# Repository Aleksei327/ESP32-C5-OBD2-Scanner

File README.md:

# ESP32-C5 OBD2 Scanner

[Русская версия](README.ru.md)

A DIY dual-CAN OBD2 diagnostic adapter built on the Seeed XIAO ESP32-C5, together with a read-only Android app. The first target is my own Citroën C3 II (2011, 1.4 KFT): ECU list, fault codes (read and clear), live data, freeze frames, a bus monitor and a PDF report. Other cars are added through a JSON knowledge base, without changing the firmware.

> **Status (November 2026): working, tested on the car.** Board v1 is built into its OBD2 enclosure, the firmware and app 0.1.5 are finished for the C3 II, and the whole chain has been used on the car: on 2 and 3 November full scans found 10 ECUs, fault codes were read with their texts, live data and an A/C test were recorded. Release: [v1.0](https://github.com/Aleksei327/ESP32-C5-OBD2-Scanner/releases/tag/v1.0).

## What works

- **Hardware:** single-sided 40 × 60 mm home-etched board in an OBD2 enclosure. Measured: on the car's OBD socket 13.4 V engine off and 14.4 V running; on the bench 4.95 V after the LM2596 and 4.83 V at the XIAO. The battery voltage reads within 0.05 V. Both CAN channels pass the self-test; the transmitters stay off in hardware until the firmware enables them.
- **Firmware** (ESP-IDF 6.1): Wi-Fi access point with its own password, WebSocket protocol, both CAN channels (OBD 6/14 and 3/8), ISO-TP with the PSA "response pending" handled, bus monitor, battery voltage, USB console with a self-test.
- **App 0.1.5** (Android): auto scan of every ECU in the knowledge base; ECU model recognised by part number; fault codes with texts from PSA-RE, the generic SAE list and, if built locally, the PSA code list in Russian and English; fault clearing; identification, live data, settings (read only); gauges, numbers and charts; bus monitor; PDF report. Scans are saved on the phone with a history (10 per car), a single module can be rescanned, and the garage and saved scans open without the adapter. The phone keeps its mobile internet while on the adapter's Wi-Fi.
- **Remote work:** a computer at home reaches the adapter at the car through the phone and a Cloudflare tunnel; `remote/scan.py` writes a full read-only scan to a report.
- **Simulator:** a C3 II in Python, to develop and test the app without the car.

Next: CAN-FD transceivers in board v2, and more cars through the knowledge base.

## The app

| | | |
| --- | --- | --- |
|  |  |  |
|  |  |  |

App 0.1.3 in English. For these screenshots it is connected to the adapter simulator ([`sim/`](sim/README.md)), not to the car, so the ECUs and values are simulated.

## The board

| | | |
| --- | --- | --- |
|  |  |  |

The real board from the copper side (two SN65HVD230, the LM2596 and the SMD parts are on this side) and the KiCad 3D view of the component side. Schematic and layout: [`hardware/scaner_v1/`](hardware/scaner_v1/README.md).

## Key decisions

| What | Choice | Why |
| --- | --- | --- |
| MCU | Seeed XIAO ESP32-C5 | two CAN (TWAI) controllers, both CAN-FD capable; Wi-Fi 6 on 2.4 and 5 GHz; BLE; 8 MB PSRAM |
| CAN channel A | OBD 6/14 | legislated OBD-II (engine) |
| CAN channel B | OBD 3/8 | PSA Diag-on-CAN through the BSI, access to every ECU |
| Transceivers | 2 × SN65HVD230 (SOIC-8), desoldered from Waveshare modules | 3.3 V, enough for the C3; Rs on D9/D5 with pull-ups gives a hardware listen-only mode. CAN-FD transceivers in v2 |
| Power | OBD 16 → fuse → HS1M → IRFB4110 source follower (≤ 27 V) → LM2596S-ADJ (4.9 V) → SS34 (+ 1.5KE6.8CA TVS) → 3.3 V LDO on the XIAO | all from parts in stock; survives a 24 V jump start and surges up to 100 V |
| Hardware | own single-sided 40 × 60 mm board inside an OBD2 enclosure with a built-in connector; tracks on the bottom only, no jumpers | one dongle, no cables |
| App | Flutter for Android (Galaxy A55): read-only plus fault-code clearing; two themes; Russian and English | |
| Link | Wi-Fi, JSON over WebSocket; the adapter is a "dumb" transport, all logic lives in the app | a new car is a new JSON file |

## Repository

| Folder | Contents |
| --- | --- |
| [`hardware/scaner_v1/`](hardware/scaner_v1/README.md) | KiCad 10 project: schematic, PCB, footprints, 3D models, and the Python scripts that generate and route the board; PDF exports in `build/` |
| [`firmware/scaner_fw/`](firmware/scaner_fw/README.md) | ESP-IDF 6.1 adapter firmware: Wi-Fi access point and WebSocket server for the app, both CAN channels, battery voltage |
| [`app/`](app/README.md) | Flutter app |
| [`sim/`](sim/README.md) | Python simulator of the adapter with a C3 attached, to develop the app without hardware or a car |
| [`remote/`](remote/README.md) | remote assistant: a computer at home works with the adapter at the car through the phone and a Cloudflare tunnel |
| [`DOCS/en/`](DOCS/en/) | documentation in English ([`DOCS/`](DOCS/) — Russian originals) |

## Documentation

- [Board v1](DOCS/en/board-v1.md): block diagram, enclosure, OBD wiring, pin assignment, layout notes, first power-up
- [Input protection](DOCS/en/power-protection.md): what the car's electrical system does to pin 16 and how the board survives it
- [LM2596 DC-DC](DOCS/en/dc-dc-5v.md): parts and values
- [XIAO ESP32-C5](DOCS/en/xiao-esp32c5.md): pinout and which pins are used
- [SN65HVD230 transceiver](DOCS/en/can-sn65hvd230.md): wiring, listen-only mode, terminators
- [Adapter ↔ app protocol](DOCS/en/protocol.md)
- [Parts list](DOCS/en/parts-list.md)

PDF exports: [schematic](hardware/scaner_v1/build/scaner_v1.pdf), [placement and copper](hardware/scaner_v1/build/pcb_placement.pdf), [bottom copper 1:1 for etching](hardware/scaner_v1/build/pcb_bottom_cu.pdf).

## What is known about the C3 (PSA, AEE2004/2010 architecture)

- Full diagnostics run on pins **3/8** (Diag-on-CAN, 500 kbit/s) through the BSI. Pins **6/14** only give legislated engine OBD-II.
- Protocols: PSA-style KWP2000 (almost every ECU of the C3 II) and UDS, both over CAN (ISO-TP). The app finds out by itself which one an ECU speaks and recognises the ECU model by its part number.
- ECU addresses (request:response): BSI `752:652`, engine `6A8:688`, ABS/ESP `6AD:68D`, airbag `744:644`, instrument cluster `75F:65F`.
- On our C3 II 1.4 KFT the engine ECU is a Valeo V34 (KWP, session `81`). Answering: BSI, engine, ABS MK70, power steering, steering-column switches, instrument cluster, display, radio, airbag, seat-belt indicator and the battery sensor (the last one often answers "busy" or stays silent).
- Terminators: pins 6–14 already have both in the car (57 Ω), pins 3–8 only the BSI one (128 Ω), so the board has R8 fitted and R7 left out.

## Rules

1. The app only reads. The only write is clearing fault codes.
2. Airbag and ABS: read only. Emissions systems are not touched.
3. The adapter is not left in the car: pin 16 is powered from the battery at all times.

## Credits and third-party work

No third-party code is copied into this repository. The app's knowledge base is generated from PSA-RE data, with extra fault-code texts from ludwig-v and OBD Codes List (see below). These projects, tools and libraries were used or consulted:

- [prototux/PSA-RE](https://github.com/prototux/PSA-RE) (Apache-2.0) — PSA electronics reverse engineering: which ECUs the C3 II has, their addresses, protocols, part numbers, data records and fault-code texts. The app's knowledge base ([`app/assets/kb/`](app/assets/kb/)) is built from it by [`app/tool/build_kb.py`](app/tool/build_kb.py); its licence text ships with the data.
- [ludwig-v/arduino-psa-diag](https://github.com/ludwig-v/arduino-psa-diag) (GPL-3.0) — PSA ECU addresses ([ECU_LIST.md](https://github.com/ludwig-v/arduino-psa-diag/blob/master/ECU_LIST.md)) and KWP/UDS commands, used as a cross-check. Its fault-code lists fill the codes PSA-RE has no text for (mostly the BSI); they ship as a separate data file under GPL-3.0, [`app/assets/kb/c3_ii_dtc_gpl.json`](app/assets/kb/c3_ii_dtc_gpl.json), with the licence text next to it.
- [OBD Codes List](https://obdcodeslist.com/code-data.html) via [tekseport/obd2-codes](https://github.com/tekseport/obd2-codes) — generic SAE J2012 fault-code texts, shown when an ECU's own list has no text for a code. Code data from OBD Codes List, https://obdcodeslist.com/code-data.html
- [KiCad](https://www.kicad.org/) and its official symbol, footprint and 3D-model libraries.
- [Freerouting](https://github.com/freerouting/freerouting) — used to explore routing (`hardware/scaner_v1/tools/route.py`); the final layout is routed by hand.
- [ESP-IDF](https://github.com/espressif/esp-idf) (Espressif) — firmware framework; [Seeed Studio wiki](https://wiki.seeedstudio.com/xiao_esp32c5_getting_started/) — XIAO ESP32-C5 pinout.
- [Flutter](https://flutter.dev/) and the Dart packages listed in [`app/pubspec.yaml`](app/pubspec.yaml): web_socket_channel, flutter_svg, google_fonts, shared_preferences, intl, image_picker, path_provider, pdf, share_plus.
- Fonts [Exo 2](https://fonts.google.com/specimen/Exo+2) and [IBM Plex](https://github.com/IBM/plex), SIL Open Font License 1.1 (licence texts in `app/assets/google_fonts/`).
- [websockets](https://github.com/python-websockets/websockets) — the simulator's WebSocket server.
- Datasheets and application data: Texas Instruments (SN65HVD230, LM2596), Espressif (ESP32-C5), Waveshare (SN65HVD230 CAN Board schematic).

Each of these keeps its own licence.

## License

See [NOTICE.md](NOTICE.md) and [LICENSE](LICENSE) (CC BY-NC-ND 4.0, with permission to build one unit for yourself).

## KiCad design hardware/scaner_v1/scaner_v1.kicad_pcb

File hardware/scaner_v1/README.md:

# Board v1 — KiCad project

[Русская версия](README.ru.md)

KiCad 10 project of the adapter board: 40 × 60 mm, single-sided (all tracks on the bottom copper, no wire jumpers), designed for home etching and built into an OBD2 enclosure. Description and design notes: [DOCS/en/board-v1.md](../../DOCS/en/board-v1.md).

| Top | Bottom |
| --- | --- |
|  |  |
|  |  |

Top row: KiCad 3D. Bottom row: the board as built, in its enclosure and from the copper side.

## Files

| Path | Contents |
| --- | --- |
| `scaner_v1.kicad_sch`, `scaner_v1.kicad_pcb`, `scaner_v1.kicad_pro` | schematic, board, project (design rules: 0.8 mm tracks, 0.4 mm clearance) |
| `scaner.pretty/` | project footprints: XIAO ESP32-C5 on two 1×7 sockets, DO-35 zener at 5.08 mm pitch, OBD2 enclosure outline |
| `scaner.3dshapes/` | hand-written 3D models (VRML) for parts missing from the KiCad library |
| `build/*.pdf` | schematic, placement with copper, bottom copper 1:1 for etching |
| `tools/` | Python scripts that generate everything (see below) |

## The board is generated, not drawn by hand

The schematic, placement and routing are produced by scripts, so a change is made in the script and everything is regenerated:

```sh
python tools/gen_schematic.py        # parts, nets, project footprints -> scaner_v1.kicad_sch
python tools/check_netlist.py        # ERC and netlist check against tools/expected_nets.json
"C:\Program Files\KiCad\10.0\bin\python.exe" tools/gen_pcb.py       # placement (PLACE table), pad rules, keep-outs
"C:\Program Files\KiCad\10.0\bin\python.exe" tools/hand_route.py    # tracks from tools/routes.py, ground pour, DRC
python tools/gen_3d.py               # 3D models into scaner.3dshapes/
```

- `routes.py` — every track as a list of points (or `REF.pad` references) with its width.
- `view_board.py` — an SVG view of the board with net names on the pads, ratsnest and DRC markers; handy while routing.
- `route.py` — Freerouting experiment kept for reference; it overwrites the hand routing.

Manual edits made in KiCad are overwritten by the next `gen_pcb.py` / `hand_route.py` run — carry them over into `routes.py` first.

**The 40 × 60 mm board for the enclosure was placed and routed by hand in KiCad** (October 2026), then etched and assembled. Do not run `gen_pcb.py` or `hand_route.py`: they bring back the old 40 × 70 board and overwrite the manual work; `routes.py` is the old routing, kept for reference. Values in the schematic and on the board match what is soldered: R1 51k, R9 200k, R11 12k, R8 fitted, R7 left out.

## Printing for etching

KiCad's Print dialog is awkward for photoresist work, so there is a print window of its own — the
"Печать для травления" button in the PCB editor (or `tools/etch_window.cmd` without KiCad):

```sh
"C:\Program Files\KiCad\10.0\bin\python.exe" tools/etch_window.py --pack      # tools/etch_print_kicad_plugin.zip for KiCad's Plugin and Content Manager
"C:\Program Files\KiCad\10.0\bin\python.exe" tools/etch_window.py --install   # while editing the code: button loaded straight from the repo (silent if the package is installed)
"C:\Program Files\KiCad\10.0\bin\python.exe" tools/etch_print.py              # no window: 4 PDFs in etch/ with an automatic layout
```

To get the button: KiCad → Plugin and Content Manager → Install from File… → `tools/etch_print_kicad_plugin.zip`.
The package lives in `Documents\KiCad\<version>\3rdparty` and survives a KiCad reinstall; after a new KiCad
version install the zip again. After changing the code, run `--pack` and reinstall the package.

- Settings on the left (scrollable), the sheet on the right; drag the divider between them.
- An A4 sheet like a print preview: drag board copies with the mouse (arrow keys move 0.5 mm), "+ copy",
  "fill the sheet"; a red frame marks copies that overlap or leave the printer's printable area.
- Negative (dry-film resist: clear = copper stays) or positive (toner transfer); "toner down / up" sets the
  mirroring: the bottom layer laid toner-to-copper prints unmirrored (KiCad shows it from the top, through the board).
- Prints straight to the printer at 1:1, no PDF viewer involved. "Film: maximum" stores a printer profile with
  the transparency media type, best quality and toner saving off; "Driver settings…" stores any driver settings
  (`%APPDATA%\etch_print`). Toner density on the HP M1530 is set in the printer's own menu.
- On the sheet: 100 mm rulers on both axes to check the scale, drill dots, crosses at mounting-hole centres,
  corner marks at the board edges. Zones are refilled before printing; the layout is kept in `etch/layout.json`.

## Enclosure

The OBD2 enclosure (72 × 46 × 26, AliExpress) is modelled from measurements by a FreeCAD script:

```sh
"C:\Program Files\FreeCAD 1.0\bin\python.exe" tools/gen_case.py      # model, drawings, enclosure layer for KiCad
"C:\Program Files\KiCad\10.0\bin\python.exe" tools/render_case.py   # pictures of the enclosure and the board inside
```

- `case/case_drawing.pdf` — dimensioned drawings (base, lid, sections, details); `*` marks assumed values.
- `case/*.step`, `case/case.FCStd` — 3D model for FreeCAD and other tools.
- `scaner.pretty/Case_OBD2_72x46` — a board-only, locked "enclosure" footprint (CASE1): the "Корпус внутри" layer
  (Eco1) shows walls, posts, plug pins and heights; "Корпус снаружи" (Eco2) the outside; a dashed outline on
  User.Drawings marks the 40 × 60 board. In the 3D viewer the enclosure is translucent, board bottom 5 mm above the floor.

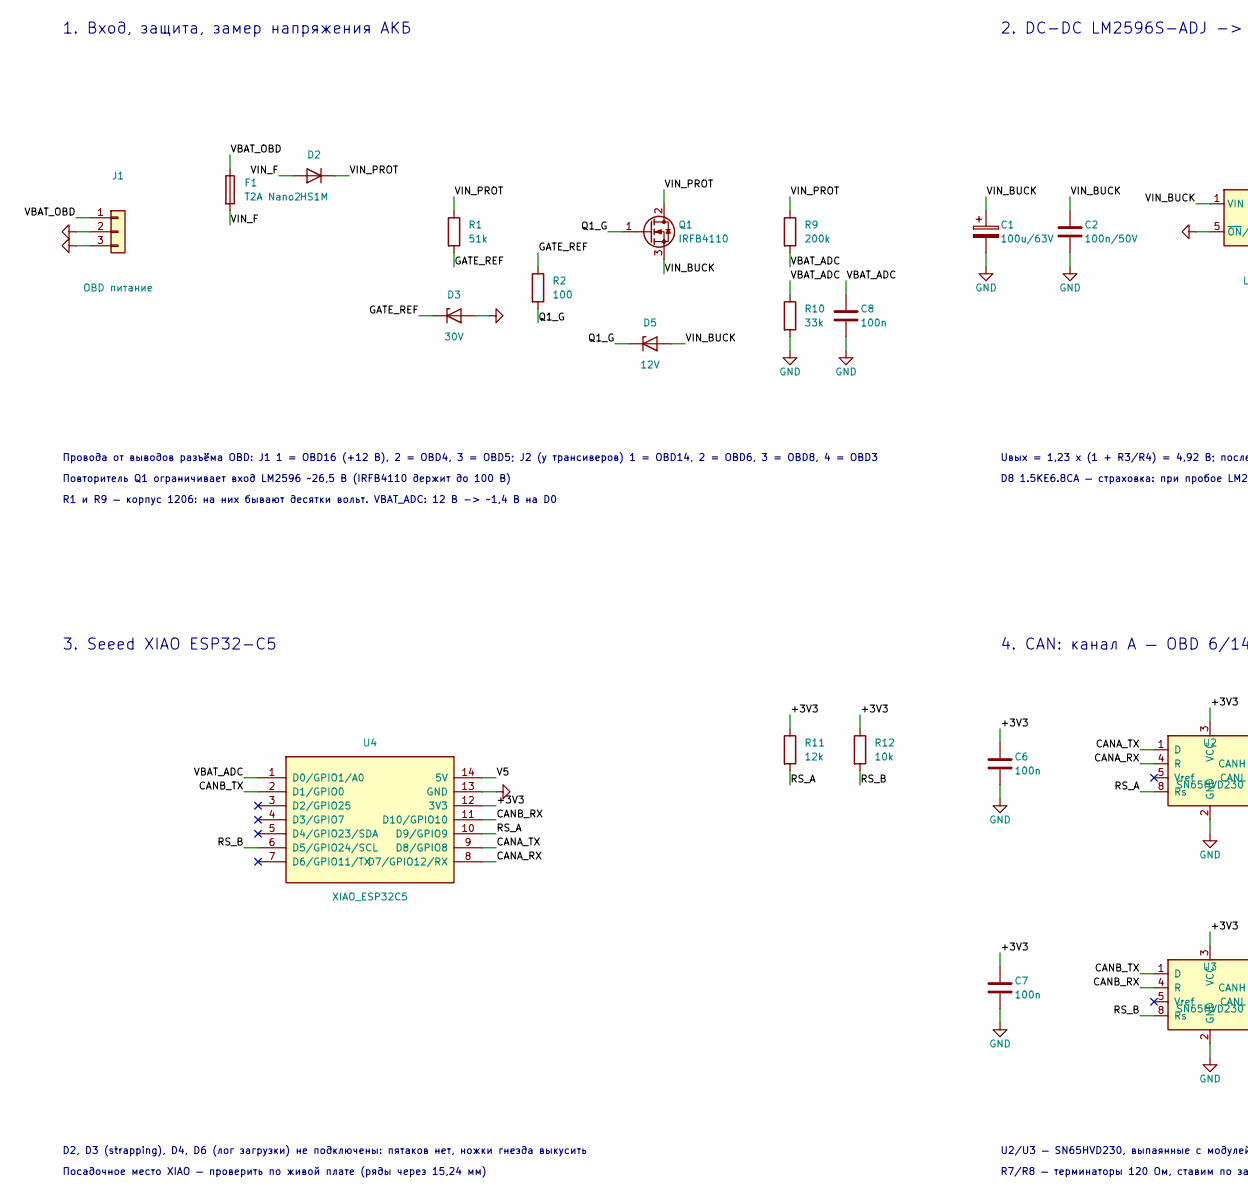
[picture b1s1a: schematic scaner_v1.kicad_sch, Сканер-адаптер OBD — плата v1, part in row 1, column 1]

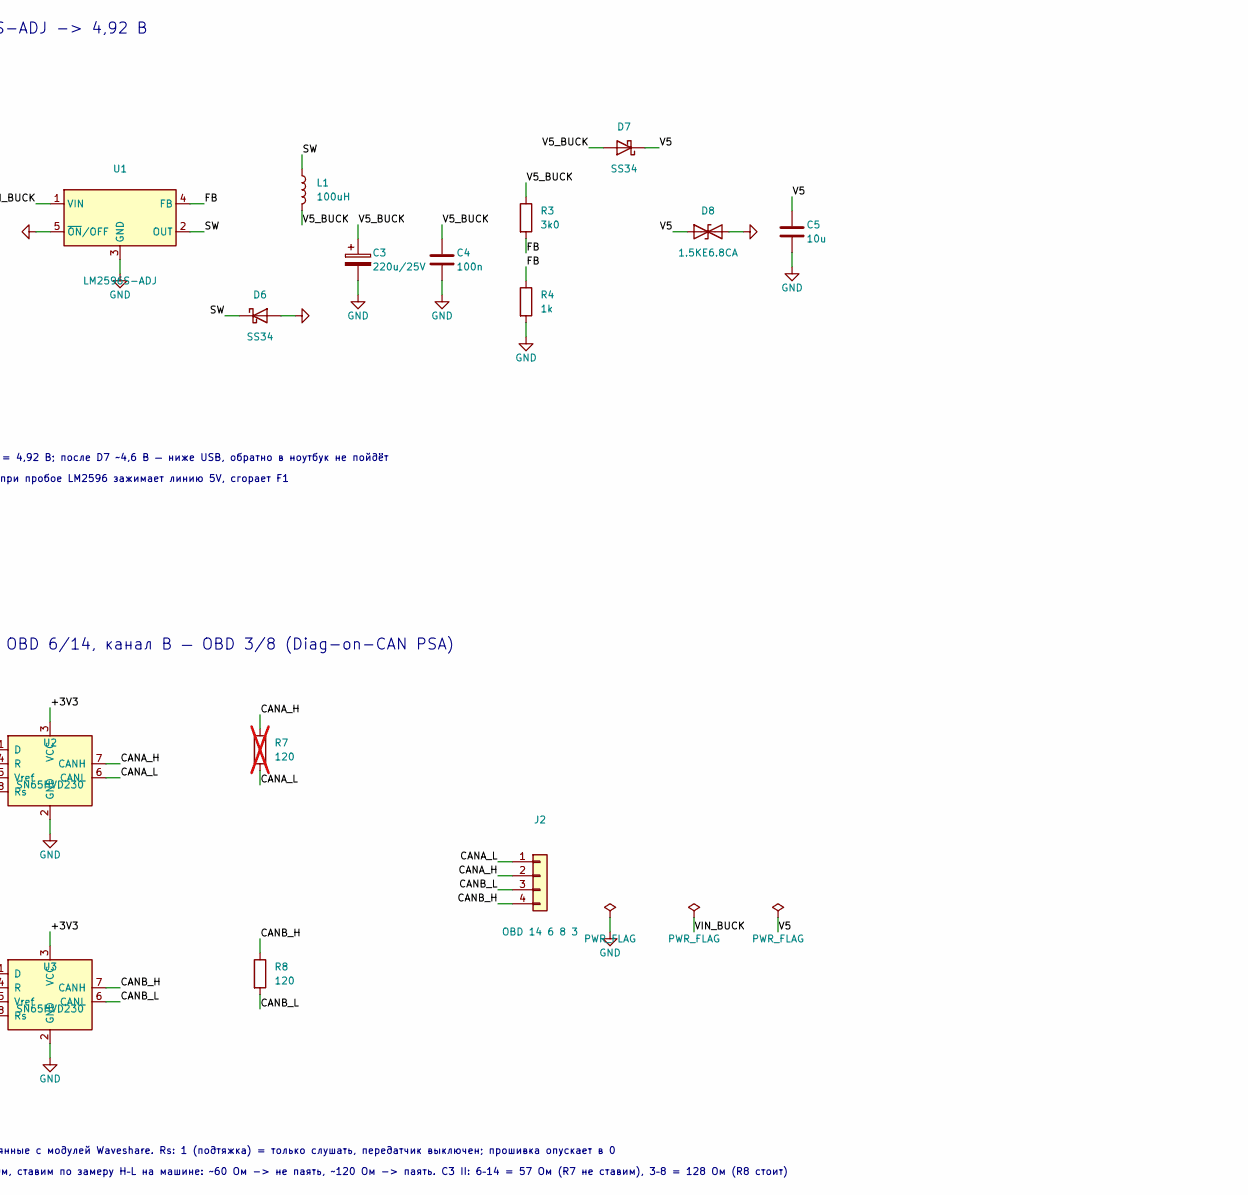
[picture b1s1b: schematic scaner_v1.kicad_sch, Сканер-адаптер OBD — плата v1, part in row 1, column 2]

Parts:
C1: 100u/63V; CP_Radial_D10.0mm_P5.00mm
C2: 100n/50V; C_1206_3216Metric
C3: 220u/25V; CP_Radial_D8.0mm_P3.50mm
C4, C6, C7, C8: 100n; C_1206_3216Metric
C5: 10u; C_1206_3216Metric
D2: HS1M; D_SMA
D3: 30V; D_DO-35_P5.08mm_Horizontal
D5: 12V; D_DO-35_P5.08mm_Horizontal
D6, D7: SS34; D_SMA
D8: 1.5KE6.8CA; D_DO-201AD_P12.70mm_Horizontal
F1: T2A Nano2; Fuse_Littelfuse-NANO2-451_453
J1: OBD питание; PinHeader_1x03_P2.54mm_Vertical
J2: OBD 14 6 8 3; PinHeader_1x04_P2.54mm_Vertical
L1: 100uH; L_Radial_D10.0mm_P5.00mm_Fastron_07P
Q1: IRFB4110; TO-220-3_Horizontal_TabDown
R1: 51k; R_1206_3216Metric
R2: 100; R_1206_3216Metric
R3: 3k0; R_1206_3216Metric
R4: 1k; R_1206_3216Metric
R7: 120; R_1206_3216Metric; not fitted
R8: 120; R_1206_3216Metric
R9: 200k; R_1206_3216Metric
R10: 33k; R_1206_3216Metric
R11: 12k; R_1206_3216Metric
R12: 10k; R_1206_3216Metric
U1: LM2596S-ADJ; TO-263-5_TabPin3
U2, U3: SN65HVD230; SOIC-8_3.9x4.9mm_P1.27mm
U4: XIAO_ESP32C5; XIAO_ESP32C5_Socket

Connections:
/+3V3: C6.1, C7.1, R11.1, R12.1, U2.3 (VCC), U3.3 (VCC), U4.12 (3V3)
/CANA_H: J2.2, R7.1, U2.7 (CANH)
/CANA_L: J2.1, R7.2, U2.6 (CANL)
/CANA_RX: U2.4 (R), U4.8 (D7/GPIO12/RX)
/CANA_TX: U2.1 (D), U4.9 (D8/GPIO8)
/CANB_H: J2.4, R8.1, U3.7 (CANH)
/CANB_L: J2.3, R8.2, U3.6 (CANL)
/CANB_RX: U3.4 (R), U4.11 (D10/GPIO10)
/CANB_TX: U3.1 (D), U4.2 (D1/GPIO0)
/FB: R3.2, R4.1, U1.4 (FB)
/GATE_REF: D3.1 (K), R1.2, R2.1
/Q1_G: D5.1 (K), Q1.1 (G), R2.2
/RS_A: R11.2, U2.8 (Rs), U4.10 (D9/GPIO9)
/RS_B: R12.2, U3.8 (Rs), U4.6 (D5/GPIO24/SCL)
/SW: D6.1 (K), L1.1, U1.2 (OUT)
/V5: C5.1, D7.1 (K), D8.1 (A1), U4.14 (5V)
/V5_BUCK: C3.1, C4.1, D7.2 (A), L1.2, R3.1
/VBAT_ADC: C8.1, R9.2, R10.1, U4.1 (D0/GPIO1/A0)
/VBAT_OBD: F1.1, J1.1
/VIN_BUCK: C1.1, C2.1, D5.2 (A), Q1.3 (S), U1.1 (VIN)
/VIN_F: D2.2 (A), F1.2
/VIN_PROT: D2.1 (K), Q1.2 (D), R1.1, R9.1
GND: C1.2, C2.2, C3.2, C4.2, C5.2, C6.2, C7.2, C8.2, D3.2 (A), D6.2 (A), D8.2 (A2), J1.2, J1.3, R4.2, R10.2, U1.3 (GND), U1.5 (~ON/OFF), U2.2 (GND), U3.2 (GND), U4.13 (GND)

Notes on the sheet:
1. Вход, защита, замер напряжения АКБ
2. DC-DC LM2596S-ADJ -> 4,92 В
3. Seeed XIAO ESP32-C5
4. CAN: канал A — OBD 6/14, канал B — OBD 3/8 (Diag-on-CAN PSA)
Провода от выводов разъёма OBD: J1 1 = OBD16 (+12 В), 2 = OBD4, 3 = OBD5; J2 (у трансиверов) 1 = OBD14, 2 = OBD6, 3 = OBD8, 4 = OBD3
Повторитель Q1 ограничивает вход LM2596 ~26,5 В (IRFB4110 держит до 100 В)
R1 и R9 — корпус 1206: на них бывают десятки вольт. VBAT_ADC: 12 В -> ~1,4 В на D0
Uвых = 1,23 x (1 + R3/R4) = 4,92 В; после D7 ~4,6 В — ниже USB, обратно в ноутбук не пойдёт
D8 1.5KE6.8CA — страховка: при пробое LM2596 зажимает линию 5V, сгорает F1
D2, D3 (strapping), D4, D6 (лог загрузки) не подключены: пятаков нет, ножки гнезда выкусить
Посадочное место XIAO — проверить по живой плате (ряды через 15,24 мм)
U2/U3 — SN65HVD230, выпаянные с модулей Waveshare. Rs: 1 (подтяжка) = только слушать, передатчик выключен; прошивка опускает в 0
R7/R8 — терминаторы 120 Ом, ставим по замеру H–L на машине: ~60 Ом -> не паять, ~120 Ом -> паять. C3 II: 6–14 = 57 Ом (R7 не ставим), 3–8 = 128 Ом (R8 стоит)

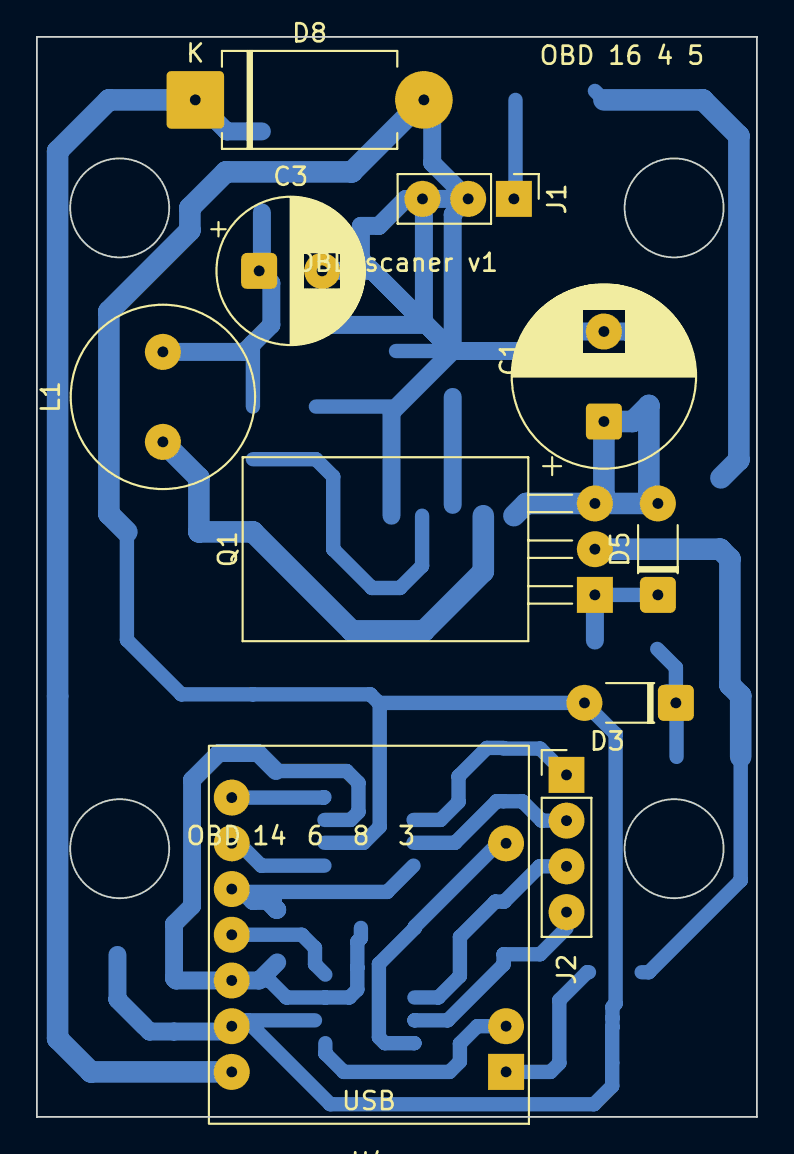
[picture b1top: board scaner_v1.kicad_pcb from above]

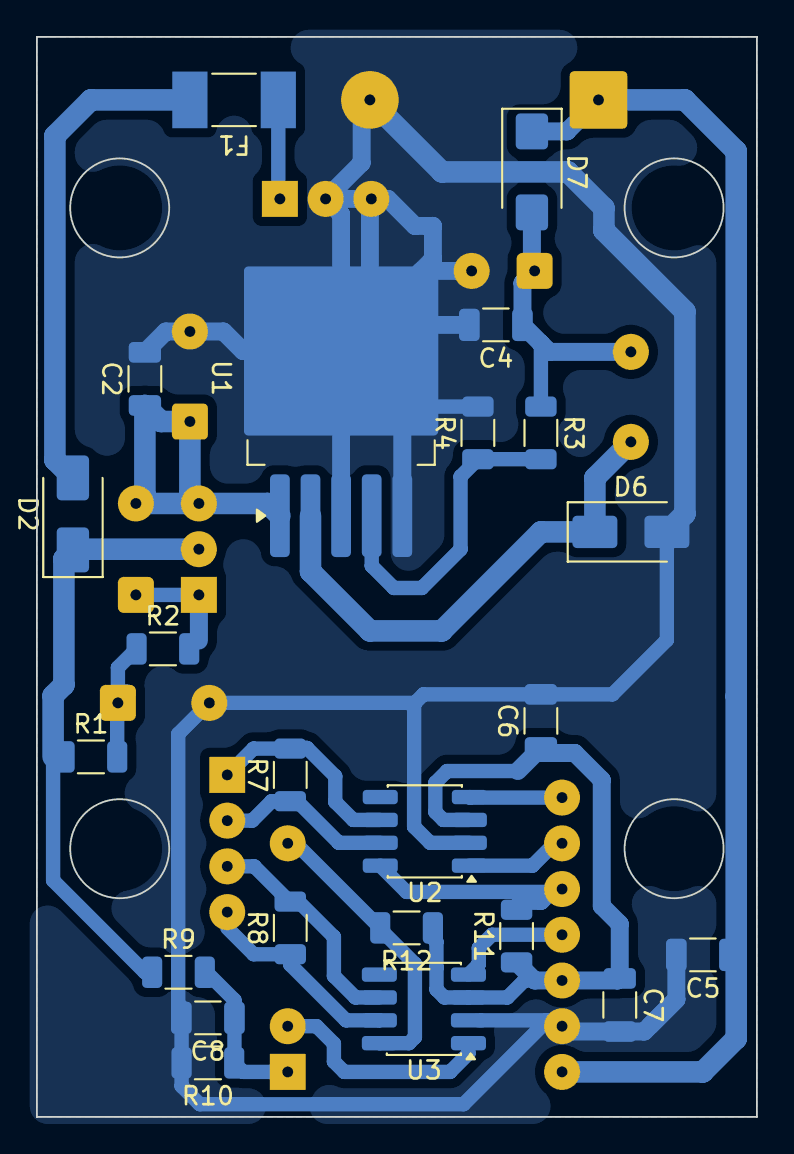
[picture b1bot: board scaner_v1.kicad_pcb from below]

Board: 2 copper layers, 40.0 x 60.0 mm, 34 parts (23 on the bottom side), 23 nets.

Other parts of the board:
CASE1: Корпус OBD2 72x46x26; Case_OBD2_72x46
